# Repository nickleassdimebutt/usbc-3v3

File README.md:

# usbc-3v3

USB-C → 3.3V LDO power board.  
Input: 5V USB-C (HRO TYPE-C-31-M-12). Output: 3.3V @ up to 800mA (AMS1117-3.3).  
Board size: 50×30mm. 2-layer, JLCPCB-compatible.

## Bill of Materials

| Ref | Value | Footprint |
|-----|-------|-----------|
| J1  | HRO TYPE-C-31-M-12 | USB-C receptacle |
| U1  | AMS1117-3.3 | SOT-223 |
| R1, R2 | 5.1kΩ | 0402 — CC pull-downs |
| C1, C2 | 10µF/10V | 0805 — VBUS bypass |
| C3  | 10µF/10V | 0805 — 3V3 output bulk |
| C4  | 100nF | 0402 — 3V3 output bypass |
| R3  | 1kΩ | 0402 — LED current limit |
| D1  | RED LED | 0805 |
| J2  | 3V3_OUT | 2-pin 2.54mm header |
| H1–H4 | — | M2 mounting holes |

---

## Verification & Bringup

### Running verification

```bash
# DRC only (fast — always run before ordering)
./verify.sh

# DRC + gerbers + drill + CPL + BOM
./verify.sh --fab

# Above + iBOM + 3D renders (needs extra KiBot deps — Linux recommended)
./verify.sh --all
```

Exit code 0 = all checks passed. Exit code 1 = one or more failures.

### Output locations

| Directory | Contents | Committed to git |
|-----------|----------|-----------------|
| `output/drc/` | DRC report (`drc_report.txt`) | ✅ yes |
| `output/render/` | 3D PNG renders (top + bottom) | ✅ yes |
| `output/ibom/` | Interactive HTML BOM | ✅ yes |
| `output/docs/` | Schematic PDF | ✅ yes |
| `output/fab/` | Gerbers, drill, CPL, BOM | ❌ no — rebuild on demand |

Committed outputs let you **diff what changed** between revisions:
```bash
git diff v1.0..v1.1 -- output/drc/drc_report.txt   # did DRC errors change?
git diff v1.0..v1.1 -- output/render/render_top.png # did the layout change?
```

### After assembly — filling out bringup.md

1. Open `bringup.md`
2. Work through each section in order (visual → continuity → smoke → rails → functional)
3. Fill in the **measured** and **pass/fail** columns as you go
4. Commit the completed checklist: `git add bringup.md && git commit -m "bringup: rev X pass"`

The checklist is pre-populated with expected values derived from the schematic (CC pull-down = 5.1kΩ to GND, 3V3 rail = 3.235–3.365V, quiescent current ≈6–10mA, etc.).

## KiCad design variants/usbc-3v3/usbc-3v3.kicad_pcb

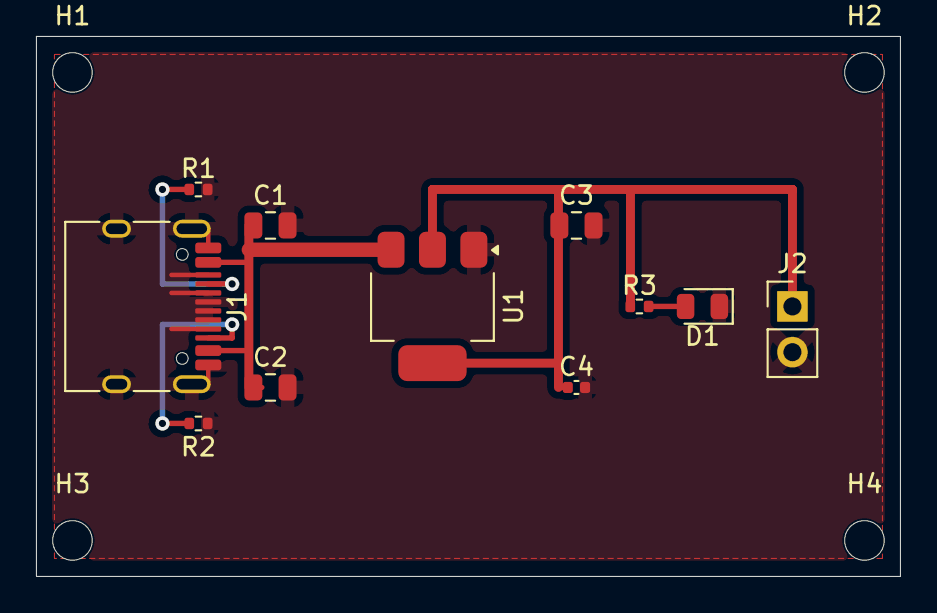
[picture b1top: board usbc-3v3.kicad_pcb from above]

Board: 2 copper layers, 48.0 x 30.0 mm, 15 parts (0 on the bottom side), 6 nets.

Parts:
C1, C2, C3: 10uF; C_0805_2012Metric
C4: 100nF; C_0402_1005Metric
D1: RED; LED_0805_2012Metric
H1, H2, H3, H4: MountingHole_M2; MountingHole_2.2mm_M2
J1: HRO TYPE-C-31-M-12; USB_C_Receptacle_HRO_TYPE-C-31-M-12
J2: 3V3_OUT; PinHeader_1x02_P2.54mm_Vertical
R1, R2: 5.1k; R_0402_1005Metric
R3: 1k; R_0402_1005Metric
U1: AMS1117-3.3; SOT-223-3_TabPin2

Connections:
+3V3: C3.1, C4.1, J2.1, R3.1, U1.2
CC1: J1.A5, R1.1
CC2: J1.B5, R2.1
GND: C1.2, C2.2, C3.2, C4.2, D1.1, J1.A1, J1.A6, J1.A7, J1.A8, J1.A12, J1.B1, J1.B6, J1.B7, J1.B8, J1.B12, J1.SH, J2.2, R1.2, R2.2, U1.1
N_D1: D1.2, R3.2
VBUS: C1.1, C2.1, J1.A4, J1.A9, J1.B4, J1.B9, U1.3

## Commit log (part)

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2026-04-28 ci: trigger rebuild against toolkit d97da1d (KiCad 9 compat)
2026-04-28 ci: install full KiCad library set + footprint debug step
2026-04-28 ci: trigger rebuild against toolkit 7b4898c (pad alias fix)
2026-04-28 ci: install libngspice0-dev for the unversioned libngspice.so symlink (PySpice needs it)
2026-04-28 ci: skip --sim on Linux runner (PySpice 1.5 incompatible with ngspice 42)
2026-04-28 ci: retry npm install -g netlistsvg up to 3 times (ECONNRESET on cold runners)
2026-04-28 ci: trigger rebuild against toolkit 86ad739 (kicad-cli auto-detect)
2026-04-29 ci: re-enable --sim now that toolkit shells out to ngspice CLI directly
2026-04-29 ci: trigger rebuild against toolkit 7f745d5 (sim/models/*.lib in package data)
